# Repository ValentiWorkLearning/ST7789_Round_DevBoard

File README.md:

# ST7789_Round_DevBoard
Board with round display based onb ST789V controller with SPI-8 bit interface.

Seller:
https://ru.aliexpress.com/item/1962405888.html?spm=a2g0o.cart.0.0.38713c00M67wvz&mp=1

Connectors:
FH26W-13S-0.3SHW (60)

Tested with drivers:
https://github.com/adafruit/Adafruit-ST7735-Library

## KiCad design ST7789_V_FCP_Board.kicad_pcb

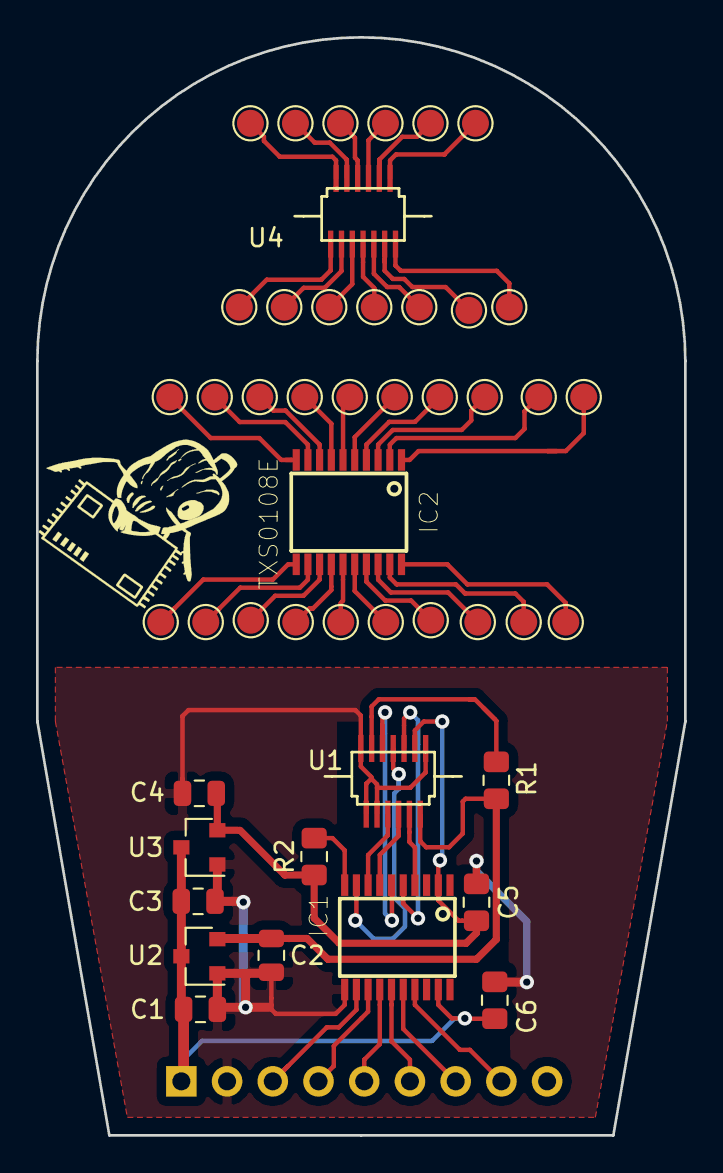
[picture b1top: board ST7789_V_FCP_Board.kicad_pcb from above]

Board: 2 copper layers, 36.0 x 61.0 mm, 48 parts (1 on the bottom side), 51 nets.

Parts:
C1, C2, C3, C4: 0.1uF; C_0805_2012Metric
C5, C6: 0.1uF; C_0805_2012Metric_Pad1.15x1.40mm_HandSolder
IC1, IC2: TXS0108E; PW_R-PDSO-G20
J1: Conn_01x08_Female; PinHeader_1x09_P2.54mm_Vertical
R1: 100R; R_0805_2012Metric_Pad1.15x1.40mm_HandSolder
R2: 10k; R_0805_2012Metric_Pad1.15x1.40mm_HandSolder
TP1, TP2, TP3, TP4, TP5, TP6, TP7, TP8, TP9, TP10, TP11, TP12, TP13, TP14, TP15, TP16, TP17, TP18, TP19, TP20, TP21, TP22, TP23, TP24, TP25, TP26, TP27, TP28, TP29, TP30, TP31, TP32, TP33: TestPoint; TestPoint_Pad_D1.5mm
U1, U4: FH26-13S-0.3SHW(05)
U2: MCP1700-2802E_SOT23; SOT-23
U3: MCP1700-1802E_SOT23; SOT-23

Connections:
/1.8V: C4.1, C5.2, IC1.2, R2.2, U1.11, U3.2
/2.8V: C2.1, R1.2, U1.12, U2.2
/CS: IC1.16, J1.7
/CS_1.8: IC1.5, U1.9
/FMARK: IC1.15, J1.6
/FMARK_1.8: IC1.6, U1.5
/LEDA: R1.1, U1.3
/RESET: IC1.17, J1.8
/RESET_1.8: IC1.4, U1.10
/RS: IC1.12, J1.3
/RS_1.8: IC1.9, U1.7
/SCLK: IC1.14, J1.5
/SCLK_1.8: IC1.7, U1.8
/SDA: IC1.13, J1.4
/SDA_1.8: IC1.8, U1.6
GND: C1.2, C2.2, C3.2, C4.2, C5.1, C6.2, IC1.11, J1.2, U1.1, U1.2, U1.4, U1.13, U2.1, U3.1
unnamed: IC1.10, R2.1
unnamed: IC2.1, TP24.1
unnamed: IC2.2, TP10.1
unnamed: IC2.3, TP25.1
unnamed: IC2.4, TP26.1
unnamed: IC2.5, TP27.1
unnamed: IC2.6, TP28.1
unnamed: IC2.7, TP29.1
unnamed: IC2.8, TP30.1
unnamed: IC2.9, TP31.1
unnamed: IC2.10, TP32.1
unnamed: IC2.11, TP33.1
unnamed: IC2.12, TP8.1
unnamed: IC2.13, TP7.1
unnamed: IC2.14, TP6.1
unnamed: IC2.15, TP5.1
unnamed: IC2.16, TP4.1
unnamed: IC2.17, TP3.1
unnamed: IC2.18, TP2.1
unnamed: IC2.19, TP9.1
unnamed: IC2.20, TP1.1
unnamed: TP11.1, U4.13
unnamed: TP12.1, U4.11
unnamed: TP13.1, U4.9
unnamed: TP14.1, U4.7
unnamed: TP15.1, U4.5
unnamed: TP16.1, U4.3
unnamed: TP17.1, U4.1
unnamed: TP18.1, U4.12
unnamed: TP19.1, U4.10
unnamed: TP20.1, U4.8
unnamed: TP21.1, U4.6
unnamed: TP22.1, U4.4
unnamed: TP23.1, U4.2
VCC: C1.1, C3.1, C6.1, IC1.19, J1.1, U2.3, U3.3
